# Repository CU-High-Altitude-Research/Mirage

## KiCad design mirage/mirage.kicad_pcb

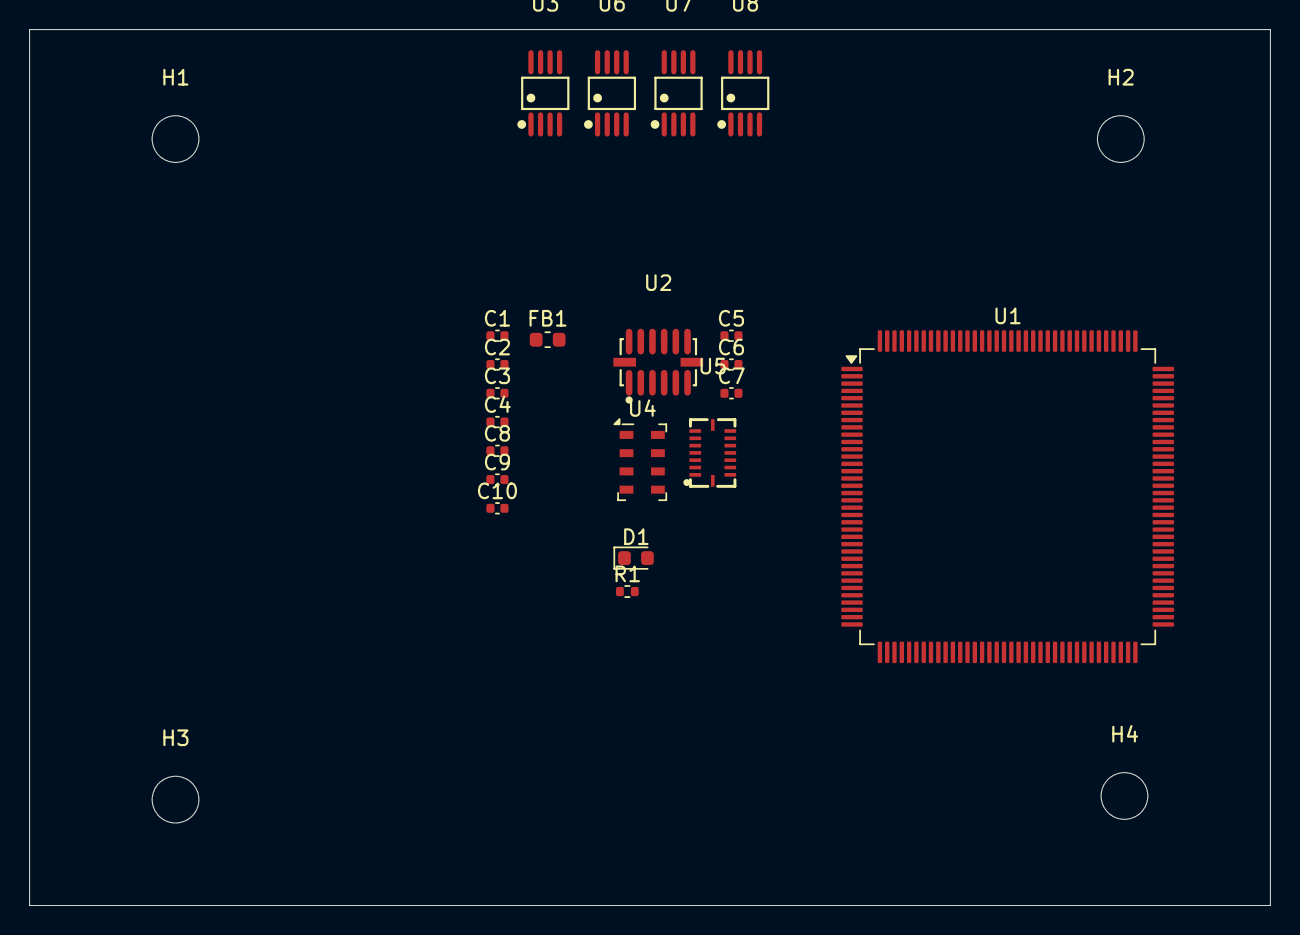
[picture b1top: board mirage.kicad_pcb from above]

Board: 2 copper layers, 85.0 x 60.0 mm, 25 parts (0 on the bottom side), 12 nets, no tracks yet.

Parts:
C1, C2, C3, C4, C5, C6, C7: 100nF; C_0402_1005Metric
C8: 100n; C_0402_1005Metric
C9, C10: 10n; C_0402_1005Metric
D1: LED Yellow; LED_0603_1608Metric
FB1: 120R; L_0603_1608Metric
H1, H2, H3, H4: MountingHole; MountingHole_3.2mm_M3
R1: 1K0R; R_0402_1005Metric
U1: STM32H573ZITx; LQFP-144_20x20mm_P0.5mm
U2: ADXL375BCCZ-RL7; LGA-14_L5.0-W3.0-P0.80-BL
U3, U6, U7, U8: TMP275AIDGKR VSSOP8; VSSOP-8_L3.0-W3.0-P0.65-LS5.0-BL
U4: MS5607-02BA; LGA-8_3x5mm_P1.25mm
U5: BMI088; LGA-16_L4.5-W3.0-P0.50-BL

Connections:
+3.3V: C1.1, C2.1, C3.1, C4.1, C5.2, C6.1, C7.1, C10.1, FB1.2, U1.17 (VDD), U1.30 (VDD), U1.39 (VDD), U1.52 (VDD), U1.62 (VDD), U1.72 (VDD), U1.84 (VDD), U1.95 (VDD), U1.108 (VDD), U1.131 (VDD), U1.144 (VDD), U3.8 (V+), U4.1 (VDD), U5.3 (VDD), U5.11 (VDDIO), U6.6 (A1), U6.8 (V+), U7.7 (A0), U7.8 (V+), U8.6 (A1), U8.7 (A0), U8.8 (V+)
+3.3VA: C8.1, C9.1, FB1.1, U1.33 (VDDA)
/Sensors/TMP275_ALERT: U3.3 (ALERT), U6.3 (ALERT), U7.3 (ALERT), U8.3 (ALERT)
/Sensors/TMP275_SCL: U3.2 (SCL), U6.2 (SCL), U7.2 (SCL), U8.2 (SCL)
/Sensors/TMP275_SDA: U3.1 (SDA), U6.1 (SDA), U7.1 (SDA), U8.1 (SDA)
BMI088_MISO: U5.10 (SDO2), U5.15 (SDO1)
GND: C1.2, C2.2, C3.2, C4.2, C5.1, C6.2, C7.2, C8.2, C9.2, C10.2, R1.2, U1.16 (VSS), U1.31 (VSSA), U1.38 (VSS), U1.51 (VSS), U1.61 (VSS), U1.71 (VSS), U1.83 (VSS), U1.94 (VSS), U1.107 (VSS), U1.120 (VSS), U1.130 (VSS), U1.143 (VSS), U2.4 (GND), U3.4 (GND), U3.5 (A2), U3.6 (A1), U3.7 (A0), U4.2 (PS), U4.3 (GND), U5.2 (NC), U5.4 (GNDA), U5.6 (GNDIO), U5.7 (PS), U6.4 (GND), U6.5 (A2), U6.7 (A0), U7.4 (GND), U7.5 (A2), U7.6 (A1), U8.4 (GND), U8.5 (A2)
MS5607_NSS: U4.4 (CSB), U4.5 (CSB)
MS5607_SCLK: U2.14 (SCL/SCLK), U4.8 (SCLK)
unnamed: D1.1 (K), R1.1
unnamed: U2.2 (GND), U2.5 (GND)
unnamed: U5.12 (INT3), U5.16 (INT1)

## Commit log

2024-09-06 feat: init repo
2024-11-05 feat: initialize structure
2025-01-10 feat(sensor): fundamental sensor lists
2025-01-16 feat: connectors
2025-02-05 Updated silkscreen
2025-02-05 feat: add some text
2025-02-05 feat: add red LED
2025-02-05 feat: add big buzzer
2025-02-05 revert: remove testing
2025-02-05 feat: testing1
2025-02-05 lolo
2025-03-11 hi hello world world hello
